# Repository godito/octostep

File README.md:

# octostep
A library for Arduino to control up to 24 StepSticks with MCP23017s through I2C on a MEGA board.
Aditionally, you can switch up to 24 peripherals through another set of MCP23017s and ULN2803s.
I also provide the board layouts in eagle.
I will add a better documentation asap. I case you want a board, I have a couple of them to spare.

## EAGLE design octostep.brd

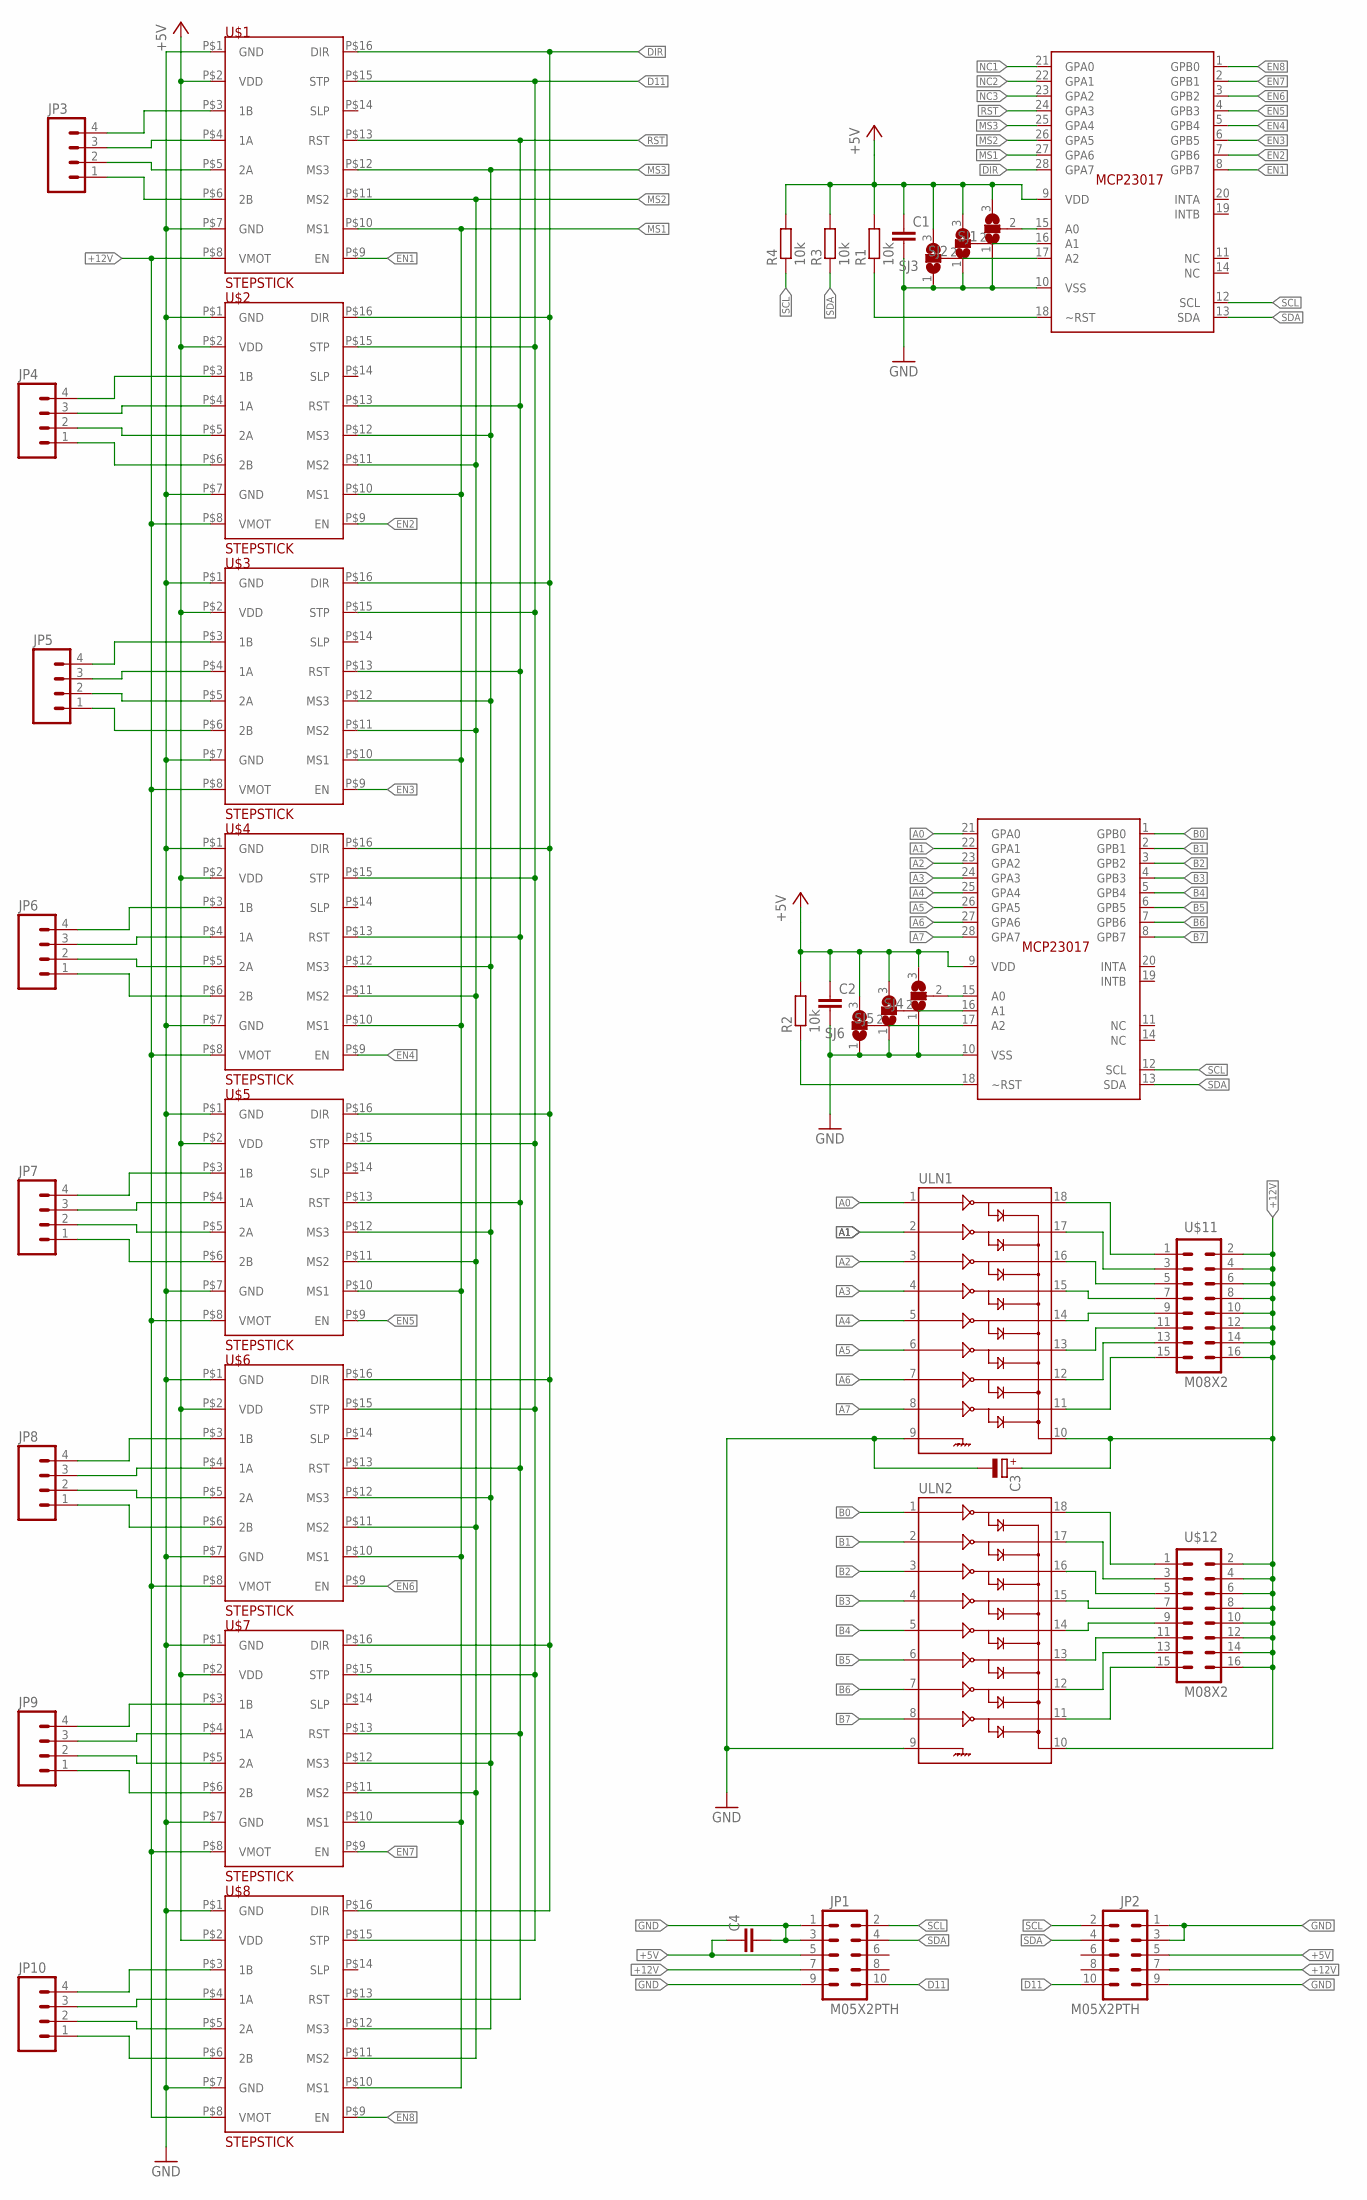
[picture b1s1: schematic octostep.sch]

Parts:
C1, C2: CAP0805; 0805
C3: CPOL-EUE3.5-10; E3,5-10
C4: C-EUC1206K; C1206K
JP1, JP2: M05X2PTH; AVR_ICSP
JP3, JP4, JP5, JP6, JP7, JP8, JP9, JP10: M04POLAR; MOLEX-1X4
R1, R2, R3, R4: 10k; R0805
SJ1, SJ2, SJ3, SJ4, SJ5, SJ6: SJ2W; SJ_2
U$1, U$2, U$3, U$4, U$5, U$6, U$7, U$8: STEPSTICK
U$9, U$10: MCP23017-E/SO; SOIC28-W_MC
U$11, U$12: M08X2; 2X8
ULN1, ULN2: ULN2803SOICW; SO18L

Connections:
+5V: C1.1, C2.1, C4.1, JP1.5, JP2.5, R1.2, R2.2, R3.2, R4.2, SJ1.3, SJ2.3, SJ3.3, SJ4.3, SJ5.3, SJ6.3, U$1.P$2 (VDD), U$2.P$2 (VDD), U$3.P$2 (VDD), U$4.P$2 (VDD), U$5.P$2 (VDD), U$6.P$2 (VDD), U$7.P$2 (VDD), U$8.P$2 (VDD), U$9.9 (VDD), U$10.9 (VDD)
+12V: C3.+, JP1.7, JP2.7, U$1.P$8 (VMOT), U$2.P$8 (VMOT), U$3.P$8 (VMOT), U$4.P$8 (VMOT), U$5.P$8 (VMOT), U$6.P$8 (VMOT), U$7.P$8 (VMOT), U$8.P$8 (VMOT), U$11.2, U$11.4, U$11.6, U$11.8, U$11.10, U$11.12, U$11.14, U$11.16, U$12.2, U$12.4, U$12.6, U$12.8, U$12.10, U$12.12, U$12.14, U$12.16, ULN1.10
A0: U$10.21 (GPA0), ULN1.1
A1: U$10.22 (GPA1), ULN1.2
A2: U$10.23 (GPA2), ULN1.3
A3: U$10.24 (GPA3), ULN1.4
A4: U$10.25 (GPA4), ULN1.5
A5: U$10.26 (GPA5), ULN1.6
A6: U$10.27 (GPA6), ULN1.7
A7: U$10.28 (GPA7), ULN1.8
B0: U$10.1 (GPB0), ULN2.1
B1: U$10.2 (GPB1), ULN2.2
B2: U$10.3 (GPB2), ULN2.3
B3: U$10.4 (GPB3), ULN2.4
B4: U$10.5 (GPB4), ULN2.5
B5: U$10.6 (GPB5), ULN2.6
B6: U$10.7 (GPB6), ULN2.7
B7: U$10.8 (GPB7), ULN2.8
D11: JP1.10, JP2.10, U$1.P$15 (STP), U$2.P$15 (STP), U$3.P$15 (STP), U$4.P$15 (STP), U$5.P$15 (STP), U$6.P$15 (STP), U$7.P$15 (STP), U$8.P$15 (STP)
DIR: U$1.P$16 (DIR), U$2.P$16 (DIR), U$3.P$16 (DIR), U$4.P$16 (DIR), U$5.P$16 (DIR), U$6.P$16 (DIR), U$7.P$16 (DIR), U$8.P$16 (DIR), U$9.28 (GPA7)
EN1: U$1.P$9 (EN), U$9.8 (GPB7)
EN2: U$2.P$9 (EN), U$9.7 (GPB6)
EN3: U$3.P$9 (EN), U$9.6 (GPB5)
EN4: U$4.P$9 (EN), U$9.5 (GPB4)
EN5: U$5.P$9 (EN), U$9.4 (GPB3)
EN6: U$6.P$9 (EN), U$9.3 (GPB2)
EN7: U$7.P$9 (EN), U$9.2 (GPB1)
EN8: U$8.P$9 (EN), U$9.1 (GPB0)
GND: C1.2, C2.2, C3.-, C4.2, JP1.1, JP1.3, JP1.9, JP2.1, JP2.3, JP2.9, SJ1.1, SJ2.1, SJ3.1, SJ4.1, SJ5.1, SJ6.1, U$1.P$1 (GND), U$1.P$7 (GND), U$2.P$1 (GND), U$2.P$7 (GND), U$3.P$1 (GND), U$3.P$7 (GND), U$4.P$1 (GND), U$4.P$7 (GND), U$5.P$1 (GND), U$5.P$7 (GND), U$6.P$1 (GND), U$6.P$7 (GND), U$7.P$1 (GND), U$7.P$7 (GND), U$8.P$1 (GND), U$8.P$7 (GND), U$9.10 (VSS), U$10.10 (VSS), ULN1.9, ULN2.9
MS1: U$1.P$10 (MS1), U$2.P$10 (MS1), U$3.P$10 (MS1), U$4.P$10 (MS1), U$5.P$10 (MS1), U$6.P$10 (MS1), U$7.P$10 (MS1), U$8.P$10 (MS1), U$9.27 (GPA6)
MS2: U$1.P$11 (MS2), U$2.P$11 (MS2), U$3.P$11 (MS2), U$4.P$11 (MS2), U$5.P$11 (MS2), U$6.P$11 (MS2), U$7.P$11 (MS2), U$8.P$11 (MS2), U$9.26 (GPA5)
MS3: U$1.P$12 (MS3), U$2.P$12 (MS3), U$3.P$12 (MS3), U$4.P$12 (MS3), U$5.P$12 (MS3), U$6.P$12 (MS3), U$7.P$12 (MS3), U$8.P$12 (MS3), U$9.25 (GPA4)
unnamed: JP3.2, U$1.P$5 (2A)
unnamed: SJ2.2, U$9.16 (A1)
unnamed: R1.1, U$9.18 (~RST)
unnamed: SJ1.2, U$9.15 (A0)
unnamed: SJ3.2, U$9.17 (A2)
unnamed: R2.1, U$10.18 (~RST)
unnamed: SJ4.2, U$10.15 (A0)
unnamed: SJ5.2, U$10.16 (A1)
unnamed: SJ6.2, U$10.17 (A2)
unnamed: JP3.3, U$1.P$4 (1A)
unnamed: JP3.4, U$1.P$3 (1B)
unnamed: JP3.1, U$1.P$6 (2B)
unnamed: JP4.2, U$2.P$5 (2A)
unnamed: JP4.3, U$2.P$4 (1A)
unnamed: JP4.4, U$2.P$3 (1B)
unnamed: JP4.1, U$2.P$6 (2B)
unnamed: JP5.2, U$3.P$5 (2A)
unnamed: JP5.3, U$3.P$4 (1A)
unnamed: JP5.4, U$3.P$3 (1B)
unnamed: JP5.1, U$3.P$6 (2B)
unnamed: JP6.2, U$4.P$5 (2A)
unnamed: JP6.3, U$4.P$4 (1A)
unnamed: JP6.4, U$4.P$3 (1B)
unnamed: JP6.1, U$4.P$6 (2B)
unnamed: JP7.2, U$5.P$5 (2A)
unnamed: JP7.3, U$5.P$4 (1A)
unnamed: JP7.4, U$5.P$3 (1B)
unnamed: JP7.1, U$5.P$6 (2B)
unnamed: JP8.2, U$6.P$5 (2A)
unnamed: JP8.3, U$6.P$4 (1A)
unnamed: JP8.4, U$6.P$3 (1B)
unnamed: JP8.1, U$6.P$6 (2B)
unnamed: JP9.2, U$7.P$5 (2A)
unnamed: JP9.3, U$7.P$4 (1A)
unnamed: JP9.4, U$7.P$3 (1B)
unnamed: JP9.1, U$7.P$6 (2B)
unnamed: JP10.2, U$8.P$5 (2A)
unnamed: JP10.3, U$8.P$4 (1A)
unnamed: JP10.4, U$8.P$3 (1B)
unnamed: JP10.1, U$8.P$6 (2B)
unnamed: U$11.1, ULN1.18
unnamed: U$11.3, ULN1.17
unnamed: U$11.5, ULN1.16
unnamed: U$11.7, ULN1.15
unnamed: U$11.9, ULN1.14
unnamed: U$11.11, ULN1.13
unnamed: U$11.13, ULN1.12
unnamed: U$11.15, ULN1.11
unnamed: U$12.1, ULN2.18
unnamed: U$12.3, ULN2.17
unnamed: U$12.5, ULN2.16
unnamed: U$12.7, ULN2.15
unnamed: U$12.9, ULN2.14
unnamed: U$12.11, ULN2.13
unnamed: U$12.13, ULN2.12
unnamed: U$12.15, ULN2.11
NC1: U$9.21 (GPA0)
NC2: U$9.22 (GPA1)
NC3: U$9.23 (GPA2)
RST: U$1.P$13 (RST), U$2.P$13 (RST), U$3.P$13 (RST), U$4.P$13 (RST), U$5.P$13 (RST), U$6.P$13 (RST), U$7.P$13 (RST), U$8.P$13 (RST), U$9.24 (GPA3)
SCL: JP1.2, JP2.2, R4.1, U$9.12 (SCL), U$10.12 (SCL)
SDA: JP1.4, JP2.4, R3.1, U$9.13 (SDA), U$10.13 (SDA)

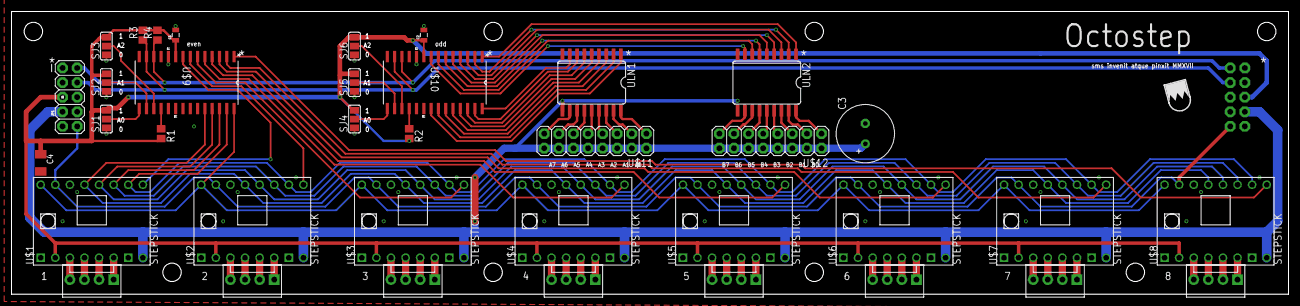
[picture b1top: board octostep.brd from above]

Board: 2 copper layers, 222.2 x 49.2 mm, 38 parts (1 on the bottom side), 91 nets.

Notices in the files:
parts and their libraries:
SparkFun-Capacitors: Licensing: CC v3.0 Share-Alike You are welcome to use this library for commercial purposes.
